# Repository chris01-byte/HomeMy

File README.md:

# HomeMy

HomeMy is a ROS 2 platform for a household robot. It is initialized as a safe, modular foundation: simulation first, explicit contracts, and controlled transfers from roboter_ws.

## Start Here

1. Read [AGENTS.md](AGENTS.md) for safety and work rules.
2. Read [CURRENT_STATE.md](CURRENT_STATE.md) for the active project state.
3. Choose one focused context area in [context/index.json](context/index.json).
4. In a local checkout, run python tools/context/brief.py --area architecture or another matching area.

## Appliance Startup

HomeMy will use one on-board Linux computer for customer operation. Developer mode retains the normal Ubuntu login and desktop. Customer mode will start the HomeMy systemd target automatically, with no customer Ubuntu login, terminal, or manual ROS command.

The customer-facing display reports boot, self-test, ready, limited-ready, or fault states with a stable error code and clear next action. The external AI server is optional for local boot: an AI outage produces limited capability, not an unsafe or blocked local startup. Power-on and ready state never authorize motion by themselves.

The current decision and contracts are [the appliance architecture decision](docs/decisions/2026-08-28-appliance-startup.md), [the system lifecycle](contracts/ros/system-lifecycle.md), [customer power-on](contracts/hardware/customer-power-on.md), and [external AI health](contracts/api/ai-server-health.md).

## Structure

| Path | Purpose |
| --- | --- |
| [src/](src/README.md) | HomeMy-owned ROS 2 packages |
| [contracts/](contracts/README.md) | Stable ROS, hardware, API, and data boundaries |
| [simulation/](simulation/README.md) | Synthetic fixtures and deterministic scenarios |
| [deployment/systemd/](deployment/systemd/README.md) | Versioned systemd target and unit templates, not yet enabled |
| [integration/roboter_ws/](integration/roboter_ws/TRANSFER_MANIFEST.md) | Controlled transfers from roboter_ws |
| [docs/](docs/README.md) | Decisions, transfers, runbooks, and archived evidence |
| [context/](context/index.json) | Token-bounded context routing for agents |
| [tools/context/](tools/context/brief.py) | Context packet generator and validator |

## Transfer Policy

HomeMy does not start as a copy of roboter_ws. Every capability transfer names an immutable source commit, target contract, dependencies, validation, risk, and rollback path before code is ported.

## Safety and Privacy

The default is simulation or motorless validation. No actor is enabled without explicit human approval. Secrets, home maps, camera data, ROS bags, and deployment-specific configuration stay outside version control.

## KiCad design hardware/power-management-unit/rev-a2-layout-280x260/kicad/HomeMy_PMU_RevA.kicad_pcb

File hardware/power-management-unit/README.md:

# HomeMy Power Management Unit (PMU)

## Verbindlicher Arbeitsstand

Die PMU ist die zentrale Energieverteilungs-, Schutz-, Mess- und Zustandssteuerung des HomeMy-Roboters.

Der nächste PCB-Arbeitsstand ist **ausschließlich 300 × 280 mm**. Frühere Verkleinerungsversuche mit 250 × 200, 275 × 210, 280 × 220 und 300 × 220 mm sind verworfen und nicht Teil dieses Arbeitsstands.

## Quellen der Wahrheit

In dieser Reihenfolge lesen:

1. `requirements.yaml` – verbindliche elektrische Werte und Statusklassen.
2. `ASTRA_PCB_HANDOFF.md` – Topologie, Schutzkonzept und Systemverhalten.
3. `interfaces-and-layout.md` – Anschlüsse, Schnittstellen und Layoutregeln.
4. `rev-a/README.md` und `rev-a/design/` – ausgearbeitete Schaltung, Bauteil- und Hochstromregeln.
5. `verification-plan.md` – Prüf- und Inbetriebnahmestrategie.
6. `ASTRA_300X280_LAYOUT.md` – begrenzter Arbeitsauftrag für das neue Layout.

## Beibehaltene Referenz

`rev-a/` ist die erfolgreiche elektrische und mechanische Referenz. Sie enthält den hierarchischen KiCad-Schaltplan, Footprints, Bauteilauswahl, Hochstromregeln, Berechnungen und überprüfbare Fertigungsgrundlagen. Ihre vorhandene Leiterplatte darf als Referenz dienen, ist aber **nicht** die Zielgeometrie des neuen Layouts.

Topologie, Netznamen, Schutzfunktionen, Bauteilwerte, Footprints, Kelvin-Verbindungen, Gate-Beschaltung, Busbar-/Press-fit-Schnittstellen und Sicherheitsregeln dürfen beim Übertragen nicht stillschweigend verändert werden.

## Aktiver Layoutauftrag

Astra erstellt einen neuen, vollständigen KiCad-PCB-Arbeitsstand in:

`hardware/power-management-unit/rev-a2-300x280/`

Die Zielkontur ist fest 300 × 280 mm. Alte kompakte Layouts dürfen weder fortgesetzt noch als CAD-Quelle kopiert werden. Der elektrische Ausgangspunkt ist der Schaltplan aus `rev-a/kicad/`.

## Freigabestatus

- Engineering-Prototyp: nach vollständiger Prüfung und menschlicher Bestellfreigabe zulässig.
- Bestromung: erst nach Schließen der in den Dokumenten genannten Energization Gates.
- Produktion/Rev B: nicht freigegeben.
- Aktorbewegung: durch diesen PCB-Auftrag nicht freigegeben.

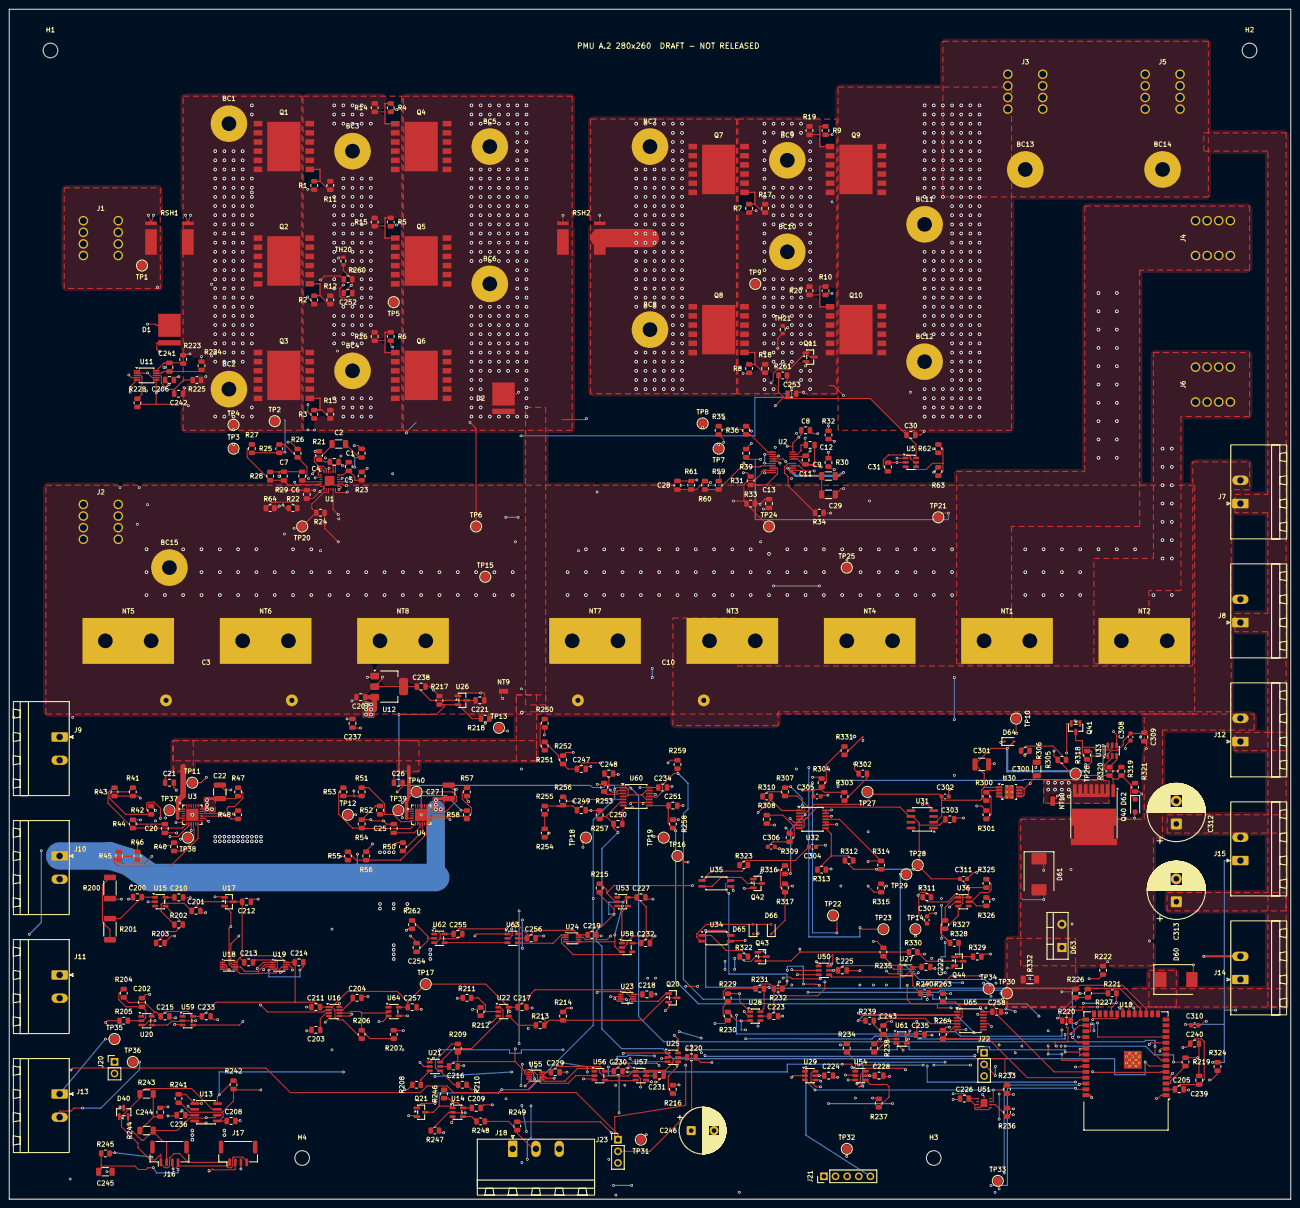
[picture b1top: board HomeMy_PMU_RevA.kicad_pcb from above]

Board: 4 copper layers, 280.0 x 260.0 mm, 425 parts (0 on the bottom side), 194 nets.

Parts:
BC1, BC2: BB1 copper clamp contact; Busbar_Contact_M3_D8
BC3, BC4: BB2 copper clamp contact; Busbar_Contact_M3_D8
BC5, BC6: BB3 copper clamp contact; Busbar_Contact_M3_D8
BC7, BC8: BB4 copper clamp contact; Busbar_Contact_M3_D8
BC9, BC10: BB5 copper clamp contact; Busbar_Contact_M3_D8
BC11, BC12, BC13, BC14: BB6 copper clamp contact; Busbar_Contact_M3_D8
BC15: BB7 copper clamp contact; Busbar_Contact_M3_D8
C1, C8, C21, C26, C30: 100nF100V X7R; C_0805_2012Metric
C2: 1uF25V X7R; C_1206_3216Metric
C3, C10: 33uF63V10% PET film; C_Rect_L31.5mm_W13mm_P27.5mm
C4, C5, C6, C7, C11, C12, C13, C31: 1nF50V5% C0G; C_0805_2012Metric
C9, C29: 4.7uF25V X7R; C_1206_3216Metric
C20, C25: 22nF50V5% C0G; C_0805_2012Metric
C22, C27: 1uF100V X7R; C_1210_3225Metric
C28: 10nF50V5% C0G; C_0805_2012Metric
C200, C205, C206, C207, C208, C209, C210, C211, C212, C213, C214, C215, C216, C217, C218, C219, C220, C221, C222, C223, C224, C225, C226, C227, C228, C229, C230, C231, C232, C233, C234, C235, C236, C240, C241, C248, C250, C251, C252, C253, C255, C256, C257, C258: 100n; C_0805_2012Metric
C201, C204, C254: 1u; C_0805_2012Metric
C202, C242, C243, C244: 10n; C_0805_2012Metric
C203: 22n; C_0805_2012Metric
C237, C238, C239: 10u; C_0805_2012Metric
C245: 1n; C_1206_3216Metric
C246: 1000u 10V; CP_Radial_D10.0mm_P5.00mm
C247, C249: 1n; C_0805_2012Metric
C300: 1uF 100V; C_1206_3216Metric
C301: 10uF 25V; C_1210_3225Metric
C302, C304, C307, C308, C310, C311: 100nF 50V; C_0603_1608Metric
C303, C309: 1uF 25V; C_0805_2012Metric
C305, C306: 100pF 50V C0G; C_0603_1608Metric
C312, C313: 470uF 100V20% high-ripple MOTION bulk; CP_Radial_D12.5mm_P5.00mm
D1, D2: 43V bidirectional low-clamp TVS; PTVS1_DFN8x6
D40: ESD2CAN24DBZRQ1; SOT-23
D60: 43V standoff TVS 1500W; D_SMC
D61: 43V drain spike clamp; D_SMC
D62: 15V gate clamp; D_SOD-123F
D63: 100V 10A resistor cable freewheel; TO-220-2_Vertical
D64: LDO reverse discharge path; D_SOD-323
D65, D66: Analog fault OR; D_SOD-323
H1, H2, H3, H4: MountingHole_3.2mm_M3
J1, J2: Battery M5 160A class; Wurth_7461103
J3: Left arm + M5 160A class; Wurth_7461103
J4: Left arm return M5 160A class; Wurth_7461103
J5: Right arm + M5 160A class; Wurth_7461103
J6: Right arm return M5 160A class; Wurth_7461103
J7: Drive 8A peak; PhoenixContact_MSTB_2,5_2-GF-5,08_1x02_P5.08mm_Horizontal_T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
J8: 24V lift-buck INPUT; PhoenixContact_MSTB_2,5_2-GF-5,08_1x02_P5.08mm_Horizontal_T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
J9: 12V PC-buck INPUT; PhoenixContact_MSTB_2,5_2-GF-5,08_1x02_P5.08mm_Horizontal_T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
J10: 5V logic-buck INPUT; PhoenixContact_MSTB_2,5_2-GF-5,08_1x02_P5.08mm_Horizontal_T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
J11: 5V converter OUTPUT return; PhoenixContact_MSTB_2,5_2-GF-5,08_1x02_P5.08mm_Horizontal_T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
J12: External resistor bank; PhoenixContact_MSTB_2,5_2-GF-5,08_1x02_P5.08mm_Horizontal_T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
J13: 24V lift clamp DNP; PhoenixContact_MSTB_2,5_2-GF-5,08_1x02_P5.08mm_Horizontal_T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
J14: Analog bank NTC; PhoenixContact_MSTB_2,5_2-GF-5,08_1x02_P5.08mm_Horizontal_T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
J15: Telemetry bank NTC; PhoenixContact_MSTB_2,5_2-GF-5,08_1x02_P5.08mm_Horizontal_T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
J16: CAN backbone IN; JST_GH_BM04B-GHS-TBT_1x04-1MP_P1.25mm_Vertical
J17: CAN backbone OUT; JST_GH_BM04B-GHS-TBT_1x04-1MP_P1.25mm_Vertical
J18: 5V LED strip 5A; PhoenixContact_MSTB_2,5_3-GF-5,08_1x03_P5.08mm_Horizontal_T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
J20: TSW-102-07-G-S; PinHeader_1x02_P2.54mm_Vertical
J21: TSW-105-07-G-S; PinHeader_1x05_P2.54mm_Vertical
J22, J23: TSW-103-07-G-S; PinHeader_1x03_P2.54mm_Vertical
NT1: ARM_L_N to BATT_N at star; NetTie_Power_2
NT2: ARM_R_N to BATT_N at star; NetTie_Power_2
NT3: DRIVE_N to BATT_N at star; NetTie_Power_2
NT4: LIFT_N to BATT_N at star; NetTie_Power_2
NT5: PC_N to BATT_N at star; NetTie_Power_2
NT6: LOGIC_BUCK_N to BATT_N at star; NetTie_Power_2
NT7: CHOPPER_N to BATT_N at star; NetTie_Power_2
NT8: LOGIC_5V_N to BATT_N at star; NetTie_Power_2
NT9: LOGIC_GND to BATT_N at star; NetTie_Logic_2
NT10: Chopper local analog reference; NetTie_Logic_2
Q1, Q2, Q3, Q4, Q5, Q6, Q7, Q8, Q9, Q10: 100V N-MOS .99mR@25C/2.3mR@175C 10V; CCPAK1212_SOT8000A
Q11: Remote temperature diode; SOT-23
Q20, Q21: BSS138BK,215; SOT-23
Q40: 100V chopper NMOS; Infineon_PG-HSOF-8-1
Q41: NTC healthy enables driver; SOT-23
Q42: Chopper gate status isolation driver; SOT-23
Q43: Qualified fault LED power; SOT-23
Q44: Qualified local enable; SOT-23
R1, R2, R3, R4, R5, R6, R7, R8, R9, R10: 10R 1%; R_0805_2012Metric
R11, R12, R13, R14, R15, R16, R17, R18, R19, R20: 10M 1%; R_0805_2012Metric
R21: 49R9 0.1% 25ppm/K; R_0805_2012Metric
R22: 18K2 0.1% 25ppm/K; R_0805_2012Metric
R23: 3K65 0.1% 25ppm/K; R_0805_2012Metric
R24, R33: 100K 0.1% 25ppm/K; R_0805_2012Metric
R25: 523K 0.1% 25ppm/K; R_0805_2012Metric
R26: 10K1 0.1% 25ppm/K; R_0805_2012Metric
R27: 732K 0.1% 25ppm/K; R_0805_2012Metric
R28, R36, R42, R44, R48, R52, R54, R58, R59, R61, R63: 10K 0.1% 25ppm/K; R_0805_2012Metric
R29, R45, R55: 1M 1%; R_0805_2012Metric
R30: 100R 0.1% 25ppm/K; R_0805_2012Metric
R31: 39K7 0.1% 25ppm/K; R_0805_2012Metric
R32: 2K74 0.1% 25ppm/K; R_0805_2012Metric
R34: 180K 1%; R_0805_2012Metric
R35, R62: 226K 0.1% 25ppm/K; R_0805_2012Metric
R39: 100K 1%; R_0805_2012Metric
R40: 6K04 0.1% 25ppm/K; R_0805_2012Metric
R41, R47, R51, R57: 191K 0.1% 25ppm/K; R_0805_2012Metric
R43, R53: 374K 0.1% 25ppm/K; R_0805_2012Metric
R46, R56: 68K 1%; R_0805_2012Metric
R50: 9K09 0.1% 25ppm/K; R_0805_2012Metric
R60: 20K 0.1% 25ppm/K; R_0805_2012Metric
R64: 200R 0.1% 25ppm/K; R_0805_2012Metric
R200, R201: 4.99k; R_2010_5025Metric
R202: 174k; R_0805_2012Metric
R203, R204, R212, R214, R219, R222, R234, R235, R236, R238, R247, R249, R250, R251, R253, R254, R255, R257, R258, R259, R263, R264: 100k; R_0805_2012Metric
R205, R218, R239, R240: 1k; R_0805_2012Metric
R206, R215: 47k; R_0805_2012Metric
R207, R209, R245: 1M; R_0805_2012Metric
R208: 120k; R_0805_2012Metric
R210: 887k; R_0805_2012Metric
R211, R213, R216, R217, R220, R221, R228, R229, R230, R231, R232, R233, R237, R241, R242, R246, R252, R256, R260, R261: 10k; R_0805_2012Metric
R223, R224, R225: 10; R_0805_2012Metric
R226, R227, R262: 4.7k; R_0805_2012Metric
R243, R244: 60.4; R_1206_3216Metric
R248: 330; R_0805_2012Metric
R300: 75.0k 0.1%; R_0805_2012Metric
R301, R304, R307, R309, R310, R311, R313, R316, R318, R324, R327: 10.0k 0.1%; R_0805_2012Metric
R302: 160k 0.1%; R_0805_2012Metric
R303: 1.40k 0.1%; R_0805_2012Metric
R305, R306: 1.00M 0.1%; R_0805_2012Metric
R308: 174k 0.1%; R_0805_2012Metric
R312: 90.9k 0.1%; R_0805_2012Metric
R314, R328: 1.00k 0.1%; R_0805_2012Metric
R315, R317, R329, R330: 100k 0.1%; R_0805_2012Metric
R319: 10.0 0.1%; R_0805_2012Metric
R320: 2.20 1%; R_0805_2012Metric
R321: 47.0k 0.1%; R_0805_2012Metric
R322, R323: 4.70k 0.1%; R_0805_2012Metric
R325: 117k 0.1%; R_0805_2012Metric
R326: 24.9k 0.1%; R_0805_2012Metric
R331: 690k 0.1%; R_0805_2012Metric
R332: 22.0k1% motion-bulk discharge; R_1206_3216Metric
RSH1, RSH2: 0.5mR 1% four-terminal10W@70C terminal; CSS4J_4026_Kelvin
TH20, TH21: 10k NTC B3380 1%; R_0603_1608Metric
TP1: BATT_FUSED_P; TestPoint_Pad_D2.0mm
TP2: BATT_SENSED_P; TestPoint_Pad_D2.0mm
TP3: MAIN_KELVIN_P; TestPoint_Pad_D2.0mm
TP4: MAIN_KELVIN_N; TestPoint_Pad_D2.0mm
TP5: MAIN_COMMON; TestPoint_Pad_D2.0mm
TP6: SYS_BUS_P; TestPoint_Pad_D2.0mm
TP7: MOTION_KELVIN_P; TestPoint_Pad_D2.0mm
TP8: MOTION_KELVIN_N; TestPoint_Pad_D2.0mm
TP9: MOTION_COMMON; TestPoint_Pad_D2.0mm
TP10: MOTION_BUS_P; TestPoint_Pad_D2.0mm
TP11: PC_BUCK_IN_P; TestPoint_Pad_D2.0mm
TP12: LOGIC_BUCK_IN_P; TestPoint_Pad_D2.0mm
TP13: V5V; TestPoint_Pad_D2.0mm
TP14: V3V3; TestPoint_Pad_D2.0mm
TP15: BATT_N; TestPoint_Pad_D2.0mm
TP16: LOGIC_GND; TestPoint_Pad_D2.0mm
TP17: AON_3V3; TestPoint_Pad_D2.0mm
TP18: AON_WAKE_EN; TestPoint_Pad_D2.0mm
TP19: MAIN_FAULT_N; TestPoint_Pad_D2.0mm
TP20: MAIN_TMR; TestPoint_Pad_D2.0mm
TP21: MOTION_GATE_EN; TestPoint_Pad_D2.0mm
TP22: MOTION_FLT_N; TestPoint_Pad_D2.0mm
TP23: MOTION_TEMP_FLT_N; TestPoint_Pad_D2.0mm
TP24: MOTION_TMR; TestPoint_Pad_D2.0mm
TP25: MOTION_IMON_INPUT; TestPoint_Pad_D2.0mm
TP26: CHOP_GATE; TestPoint_Pad_D2.0mm
TP27: CHOP_10V; TestPoint_Pad_D2.0mm
TP28: CHOP_REF2V5; TestPoint_Pad_D2.0mm
TP29: CHOP_FAULT_N; TestPoint_Pad_D2.0mm
TP30: CHOP_ACTIVE_N; TestPoint_Pad_D2.0mm
TP31: CAN_TX; TestPoint_Pad_D2.0mm
TP32: CAN_RX; TestPoint_Pad_D2.0mm
TP33: ESP_MAIN_HOLD; TestPoint_Pad_D2.0mm
TP34: ESP_MOTION_RESET; TestPoint_Pad_D2.0mm
TP35: LIFT_24V_SAMPLE; TestPoint_Pad_D2.0mm
TP36: LIFT_24V_N; TestPoint_Pad_D2.0mm
TP37: PC_EFUSE_FAULT_N; TestPoint_Pad_D2.0mm
TP38: PC_EFUSE_PGOOD; TestPoint_Pad_D2.0mm
TP39: LOGIC_EFUSE_FAULT_N; TestPoint_Pad_D2.0mm
TP40: LOGIC_EFUSE_PGOOD; TestPoint_Pad_D2.0mm
U1: LM74930-Q1; VQFN_RGE24_4x4_P0.5_EP_FLOAT
U2: TPS48110-Q1; VSSOP_DGX19_3x5.1_P0.5_Missing16
U3, U4: TPS26631 eFuse latch-off; Texas_RGE0024H_VQFN-24-1EP_4x4mm_P0.5mm_EP2.7x2.7mm
U5: Latched motion SYS undervoltage detector; SOT-23-6
U10: ESP32-S3-WROOM-1-N8; ESP32-S3-WROOM-1
U11: INA228AIDGSR; MSOP-10_3x3mm_P0.5mm
U12: TLV1117LV33DCYR; SOT-223-3_TabPin2
U13: TCAN1042HGVDRQ1; SOIC-8_3.9x4.9mm_P1.27mm
U14: SN74AHCT1G125DBVR; SOT-23-5
U15: LT3014BIS5#TRPBF; SOT-23-5
U16: LTC2954ITS8-1#TRPBF; TSOT-23-8
U17, U26: TPS3839G33DBZR; SOT-23
U18, U23, U27, U55: SN74LVC1G74DCUR; VSSOP-8_2.3x2mm_P0.5mm
U19, U24: SN74LVC2G00DCUR; VSSOP-8_2.3x2mm_P0.5mm
U20, U53, U56, U59: SN74LVC1G14DBVR; SOT-23-5
U21: LTC6993IS6-1#TRPBF; TSOT-23-6
U22, U58: SN74LVC1G32DBVR; SOT-23-5
U25, U28, U29, U50, U54, U57, U63: SN74LVC1G11DBVR; SOT-23-6
U30: 100V LDO, nominal 10V; Texas_DGN0008B_VSSOP-8-1EP_3x3mm_P0.65mm_EP2x3mm_Mask1.88x1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
U31: 2.5V high-grade reference; SOIC-8_3.9x4.9mm_P1.27mm
U32: Independent analog chopper/OV/NTC window; TSSOP-14_4.4x5mm_P0.65mm
U33: 4A source/8A sink driver; SOT-23-6
U34: Isolated analog fault; SSOP-4_4.4x2.6mm_P1.27mm
U35: Isolated chopper active; SSOP-4_4.4x2.6mm_P1.27mm
U36: Reference qualification 12..28ms; SOT-23-6
U51: TPS3431SDRBR; TI_DRB0008A_3x3mm_EP1.5x1.75
U60, U65: TMUX1511PWR; TSSOP-14_4.4x5mm_P0.65mm
U61, U62, U64: SN74LVC1G17DBVR; SOT-23-5

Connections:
AON_3V3: C201.1, C210.1, C211.1, C212.1, C213.1, C214.1, C215.1, C216.1, C217.1, C218.1, C219.1, C220.1, C227.1, C229.1, C230.1, C231.1, C232.1, C233.1, C255.1, C256.1, C257.1, R202.1, R204.1, R206.1, R209.1, R215.1, TP17.1, U15.5, U16.1, U17.3, U18.8, U19.8, U20.5, U21.5, U22.5, U23.8, U24.8, U25.5, U53.5, U55.2, U55.7, U55.8, U56.5, U57.5, U57.6, U58.5, U59.5, U62.5, U63.5, U64.5
AON_FB: R202.2, R203.1, U15.4
AON_FEED_MID: R200.2, R201.1
AON_LDO_IN: C200.1, R201.2, U15.1
AON_RESET_N: U17.2, U18.6, U19.2, U25.6, U63.6
AON_WAKE_EN: R29.1, R216.1, TP18.1, U1.6, U1.7, U25.4, U50.6, U54.6
ARM_L_N: J4.1, J4.2, J4.3, J4.4, J4.5, J4.6, J4.7, J4.8, NT1.1
ARM_R_N: J6.1, J6.2, J6.3, J6.4, J6.5, J6.6, J6.7, J6.8, NT2.1
BATT_FUSED_P: D1.1, J1.1, J1.2, J1.3, J1.4, J1.5, J1.6, J1.7, J1.8, RSH1.1, TP1.1
BATT_N: BC15.1, C1.2, C3.2, C6.2, C7.2, C8.2, C10.2, C13.2, C20.2, C21.2, C22.2, C25.2, C26.2, C27.2, C28.2, D1.2, D2.2, J2.1, J2.2, J2.3, J2.4, J2.5, J2.6, J2.7, J2.8, NT1.2, NT2.2, NT3.2, NT4.2, NT5.2, NT6.2, NT7.2, NT8.2, NT9.2, Q11.2, R24.2, R26.2, R28.2, R29.2, R31.2, R33.2, R36.2, R39.2, R40.2, R42.2, R44.2, R46.2, R48.2, R50.2, R52.2, R54.2, R56.2, R58.2, R59.2, R61.2, R64.2, TP15.1, U1.13, U1.16, U2.2, U2.6, U3.8, U3.25, U4.8, U4.25
BATT_SENSED_P: BC1.1, BC2.1, C1.1, C2.2, Q1.7, Q1.8, Q1.9, Q1.10, Q1.11, Q1.12, Q1.13, Q2.7, Q2.8, Q2.9, Q2.10, Q2.11, Q2.12, Q2.13, Q3.7, Q3.8, Q3.9, Q3.10, Q3.11, Q3.12, Q3.13, R25.1, R27.1, R200.1, R225.1, RSH1.4, TP2.1, U1.22
BUTTON_ARMED: U18.5, U19.6
BUTTON_ARM_SET_N: U18.7, U19.7
BUTTON_INT_N: R221.2, U10.23, U16.5
CAN_H: D40.1, J16.1, J17.1, R243.1, U13.7
CAN_L: D40.2, J16.2, J17.2, R244.2, U13.6
CAN_RX: TP32.1, U10.9, U13.4
CAN_STB: R242.2, U10.34, U13.8
CAN_TERM_MID: C244.1, R243.2, R244.1
CAN_TX: R241.2, TP31.1, U10.10, U13.1
CHASSIS: C245.1, J16.4, J17.4, R245.1
CHOPPER_N: C312.2, C313.2, D60.2, D61.2, NT7.1, NT10.2, Q40.2, R332.2
CHOP_10V: C301.1, C302.1, C304.1, C308.1, C309.1, D64.2, Q43.2, R300.1, R307.1, R310.1, R316.1, R318.1, R323.1, R330.1, TP27.1, U30.1, U31.2, U32.3, U33.1
CHOP_ACTIVE_LED_A: R323.2, U35.1
CHOP_ACTIVE_LED_K: Q42.3, U35.2
CHOP_ACTIVE_N: R232.2, TP30.1, U10.32, U35.4
CHOP_DISABLE: Q41.3, R318.2, U33.5
CHOP_DRAIN: D61.1, D63.2, J12.2, Q40.3
CHOP_DRIVE_H: R319.1, U33.2
CHOP_DRIVE_L: R320.1, U33.3
CHOP_FAULT_LED_A: R322.2, U34.1
CHOP_FAULT_LED_K: D65.2, D66.2, U34.2
CHOP_FAULT_N: R231.2, TP29.1, U10.31, U28.6, U34.4
CHOP_FAULT_PWR: Q43.3, R322.1
CHOP_FB: R300.2, R301.1, U30.2
CHOP_GATE: D62.1, Q40.1, Q42.1, R305.1, R319.2, R320.2, R321.1, TP26.1
CHOP_GND: C300.2, C301.2, C302.2, C303.2, C304.2, C305.2, C306.2, C307.2, C308.2, C309.2, C311.2, D62.2, J14.2, NT10.1, Q42.2, Q44.2, R301.2, R304.2, R309.2, R313.2, R315.2, R317.2, R321.2, R326.2, R329.2, U30.4, U30.9, U31.4, U32.12, U33.4, U36.2
CHOP_HYS_MID: R305.2, R306.1
CHOP_HYS_MID2: R306.2, R331.1
CHOP_NTC: C307.1, J14.1, R311.2, U32.9, U32.10
CHOP_OV_OK: D65.1, R310.2, U32.1
CHOP_OV_SENSE: C306.1, R308.2, R309.1, U32.6
CHOP_QUALIFY_BASE: Q44.1, R328.2, R329.1
CHOP_QUALIFY_N: Q41.2, Q43.1, Q44.3, R330.2
CHOP_REF2V5: C303.1, C311.1, R311.1, R312.1, R314.1, R325.1, R327.1, TP28.1, U31.6, U32.4, U32.7, U36.3, U36.6
CHOP_REF_READY: R327.2, R328.1, U36.1
CHOP_REF_SENSE: R325.2, R326.1, U36.5
CHOP_REQUEST: R307.2, U32.2, U33.6
CHOP_SENSE: C305.1, R303.2, R304.1, R331.2, U32.5
CHOP_SENSE_TOP: R302.2, R303.1
CHOP_TEMP_ADC: C310.1, J15.1, R324.2, U10.4
CHOP_TEMP_HIGH: R314.2, R315.1, U32.11
CHOP_TEMP_LOW: R312.2, R313.1, U32.8
CHOP_THERMAL_OK: D66.1, Q41.1, R316.2, R317.1, U32.13, U32.14
DRIVE_N: J7.2, NT3.1
ESP_BOOT_N: J21.4, R220.2, U10.27
ESP_CHIP_EN: J21.5, R218.2, R219.1, U10.3, U29.1
ESP_MAIN_HOLD: R211.1, R222.1, TP33.1, U10.22
ESP_MAIN_HOLD_AON: R211.2, R212.1, U22.2
ESP_MOTION_REQUEST: R234.1, U10.19, U54.1
ESP_MOTION_RESET: R235.1, TP34.1, U10.20, U27.1
ESP_UART_RX: R263.1, U10.36, U65.3
ESP_UART_TX: R264.1, U10.37, U65.6
ESP_WDI: R236.1, U10.21, U51.6
ESP_WDO_N: R233.2, U29.3, U51.7
I2C_SCL: J23.2, R227.2, U10.18, U11.5
I2C_SDA: J23.1, R226.2, U10.17, U11.4
INA_ALERT_N: R228.2, U10.33, U11.3
INA_IN_N: C241.2, R224.2, U11.9
INA_IN_P: C241.1, R223.2, U11.10
INA_VBUS: C242.1, R225.2, U11.8
KILL_HOLD_OR: R213.1, U22.4
LED_BUFFER_OUT: R248.1, U14.4
LED_DATA_3V3: R247.1, U10.11, U14.2
LED_DATA_OUT: J18.2, R248.2, R249.1
LED_OE_N: Q21.3, R246.2, U14.1
LIFT_24V_N: J13.2, TP36.1
LIFT_24V_SAMPLE: J13.1, TP35.1
LIFT_N: J8.2, NT4.1
LOGIC_5V_N: C246.2, J11.2, J18.3, NT8.1
LOGIC_BUCK_IN_P: C27.1, J10.1, R57.1, TP12.1, U4.17, U4.18
LOGIC_BUCK_N: J10.2, NT6.1
LOGIC_DVDT: C25.1, U4.9
LOGIC_EFUSE_FAULT_N: TP39.1, U4.14
LOGIC_EFUSE_PGOOD: TP40.1, U4.16
LOGIC_GND: C30.2, C31.2, C200.2, C201.2, C202.2, C203.2, C204.2, C205.2, C206.2, C207.2, C208.2, C209.2, C210.2, C211.2, C212.2, C213.2, C214.2, C215.2, C216.2, C217.2, C218.2, C219.2, C220.2, C221.2, C222.2, C223.2, C224.2, C225.2, C226.2, C227.2, C228.2, C229.2, C230.2, C231.2, C232.2, C233.2, C234.2, C235.2, C236.2, C237.2, C238.2, C239.2, C240.2, C242.2, C243.2, C244.2, C245.2, C247.2, C248.2, C249.2, C250.2, C251.2, C252.2, C253.2, C254.2, C255.2, C256.2, C257.2, C258.2, C310.2, D40.3, J15.2, J16.3, J17.3, J20.2, J21.1, J22.3, J23.3, NT9.1, Q20.2, Q21.2, R63.2, R203.2, R207.2, R208.2, R210.2, R212.2, R214.2, R216.2, R217.2, R219.2, R222.2, R234.2, R235.2, R236.2, R237.2, R238.2, R245.2, R247.2, R249.2, R252.2, R253.2, R256.2, R257.2, R258.2, R259.2, R263.2, R264.2, TH20.2, TH21.2, TP16.1, U5.2, U10.1, U10.40, U10.41, U11.1, U11.2, U11.7, U12.1, U13.2, U14.3, U15.2, U16.4, U17.1, U18.1, U18.2, U18.4, U19.4, U20.3, U21.2, U22.3, U23.1, U23.2, U23.4, U24.4, U24.5, U24.6, U25.2, U26.1, U27.4, U28.2, U29.2, U34.3, U35.3, U50.2, U51.4, U51.9, U53.3, U54.2, U55.4, U56.3, U57.2, U58.3, U59.3, U60.7, U61.3, U62.3, U63.2, U64.3, U65.7, U65.10, U65.13
LOGIC_ILIM: R50.1, U4.10
LOGIC_OVP: R53.2, R54.1, U4.7
LOGIC_PGTH: R57.2, R58.1, U4.15
LOGIC_SHDN: R55.2, R56.1, U4.12
LOGIC_UVLO: R51.2, R52.1, U4.6
MAIN_CAP: C2.1, U1.23
MAIN_CAPTURE_DELAYED: U62.4, U63.3
MAIN_CAPTURE_EN: U24.1, U63.4
MAIN_CAPTURE_RC: C254.1, R262.2, U62.2
MAIN_COMMON: BC3.1, BC4.1, Q1.2, Q1.3, Q1.4, Q1.5, Q1.6, Q2.2, Q2.3, Q2.4, Q2.5, Q2.6, Q3.2, Q3.3, Q3.4, Q3.5, Q3.6, Q4.2, Q4.3, Q4.4, Q4.5, Q4.6, Q5.2, Q5.3, Q5.4, Q5.5, Q5.6, Q6.2, Q6.3, Q6.4, Q6.5, Q6.6, R11.2, R12.2, R13.2, R14.2, R15.2, R16.2, TP5.1, U1.2, U1.15
MAIN_CS_P: C4.1, R21.2, U1.20
MAIN_DGATE: R4.1, R5.1, R6.1, U1.1
MAIN_FAULT_ANY: U24.2, U58.4
MAIN_FAULT_ASSERTED: U53.4, U58.1
MAIN_FAULT_GPIO_N: R259.1, U10.28, U60.11
MAIN_FAULT_LATCHED: Q20.1, U23.5
MAIN_FAULT_N: R215.2, TP19.1, U1.12, U53.2, U60.12
MAIN_FAULT_SET_N: U23.7, U24.7
MAIN_HGATE: R1.1, R2.1, R3.1, U1.14
MAIN_ILIM: R22.1, U1.11
MAIN_ILIM_TAIL: R22.2, R64.1
MAIN_ISCP: C5.1, R23.2, U1.18
MAIN_KELVIN_N: C4.2, C5.2, R224.1, RSH1.3, TP4.1, U1.19
MAIN_KELVIN_P: R21.1, R23.1, R223.1, RSH1.2, TP3.1
MAIN_LATCH_OK: U23.3, U25.3
MAIN_OV: C7.1, R27.2, R28.1, U1.5
MAIN_TMR: C3.1, R24.1, TP20.1, U1.9
MAIN_UVLO: C6.1, R25.2, R26.1, U1.4
MOTION_ARMED: R240.1, U27.5, U54.3
MOTION_ARMED_SENSE: R240.2, U10.35
MOTION_BST: C9.1, C29.1, U2.12
MOTION_BUS_ADC: C250.1, R257.1, U10.6, U60.6
MOTION_BUS_DIV: C249.1, R255.2, R256.1, U60.5
MOTION_BUS_P: BC11.1, BC12.1, BC13.1, BC14.1, C300.1, C312.1, C313.1, D60.1, D63.1, D64.1, J3.1, J3.2, J3.3, J3.4, J3.5, J3.6, J3.7, J3.8, J5.1, J5.2, J5.3, J5.4, J5.5, J5.6, J5.7, J5.8, J7.1, J8.1, J12.1, Q9.7, Q9.8, Q9.9, Q9.10, Q9.11, Q9.12, Q9.13, Q10.7, Q10.8, Q10.9, Q10.10, Q10.11, Q10.12, Q10.13, R254.1, R302.1, R308.1, R332.1, TP10.1, U30.5, U30.8
MOTION_CLEAR_N: U27.6, U50.4
MOTION_COMMON: BC9.1, BC10.1, C9.2, C29.2, Q7.2, Q7.3, Q7.4, Q7.5, Q7.6, Q8.2, Q8.3, Q8.4, Q8.5, Q8.6, Q9.2, Q9.3, Q9.4, Q9.5, Q9.6, Q10.2, Q10.3, Q10.4, Q10.5, Q10.6, R17.2, R18.2, R19.2, R20.2, TP9.1, U2.13
MOTION_CS_P: C11.1, R30.2, U2.18
MOTION_FAULTS_OK: U28.4, U50.3
MOTION_FLT_N: R229.2, TP22.1, U2.5, U5.1, U10.29, U28.1
MOTION_GATE_DRIVE: R7.1, R8.1, R9.1, R10.1, R34.2, U2.14
MOTION_GATE_EN: R39.1, R237.1, TP21.1, U2.3, U54.4
MOTION_IMON_ADC: C251.1, R258.1, U10.5, U60.8
MOTION_IMON_INPUT: C28.1, R60.2, R61.1, TP25.1, U60.9
MOTION_IMON_RAW: R59.1, R60.1, U2.7
MOTION_ISCP: C12.1, R32.2, U2.19
MOTION_IWRN: R31.1, U2.8
MOTION_KELVIN_N: C11.2, C12.2, RSH2.3, TP8.1, U2.17
MOTION_KELVIN_P: R30.1, R32.1, RSH2.2, TP7.1
MOTION_LATCH_UV_SENSE: R62.2, R63.1, U5.3
MOTION_LOCAL_OK: U29.4, U50.1
MOTION_PERMIT: U29.6, U61.4
MOTION_PERMIT_CONNECTOR: J22.2, R239.1
MOTION_PERMIT_RAW: C243.1, R238.1, R239.2, U61.2
MOTION_PU: R34.1, U2.15
MOTION_SENSED_P: BC7.1, BC8.1, Q7.7, Q7.8, Q7.9, Q7.10, Q7.11, Q7.12, Q7.13, Q8.7, Q8.8, Q8.9, Q8.10, Q8.11, Q8.12, Q8.13, RSH2.4
MOTION_TEMP_DIODE: C13.1, Q11.1, Q11.3, U2.10
MOTION_TEMP_FLT_N: R230.2, TP23.1, U2.4, U10.30, U28.3
MOTION_TMR: C10.1, R33.1, TP24.1, U2.9
MOTION_UVLO: R35.2, R36.1, U2.1
MOTION_UV_REF: C31.1, U5.4, U5.5
MOT_DIV_MID: R254.2, R255.1
PB_CONNECTOR: J20.1, R205.1
PB_LTC_N: U16.2, U19.3
PB_PRESSED: U19.5, U20.4, U59.2
PB_RAW_N: C202.1, R204.2, R205.2, U20.2
PB_RELEASED: U19.1, U59.4
PC_BUCK_IN_P: C22.1, J9.1, R47.1, TP11.1, U3.17, U3.18
PC_DVDT: C20.1, U3.9
PC_EFUSE_FAULT_N: TP37.1, U3.14
PC_EFUSE_PGOOD: TP38.1, U3.16
PC_ILIM: R40.1, U3.10
PC_N: J9.2, NT5.1
PC_OVP: R43.2, R44.1, U3.7
PC_PGTH: R47.2, R48.1, U3.15
PC_SHDN: R45.2, R46.1, U3.12
PC_UVLO: R41.2, R42.1, U3.6
Q1_G: Q1.1, R1.2, R11.1
Q2_G: Q2.1, R2.2, R12.1
Q3_G: Q3.1, R3.2, R13.1
Q4_G: Q4.1, R4.2, R14.1
Q5_G: Q5.1, R5.2, R15.1
Q6_G: Q6.1, R6.2, R16.1
Q7_G: Q7.1, R7.2, R17.1
Q8_G: Q8.1, R8.2, R18.1
Q9_G: Q9.1, R9.2, R19.1
Q10_G: Q10.1, R10.2, R20.1
STARTUP_DIV: R209.2, R210.1, U21.4
STARTUP_GRANT: U21.6, U22.1
STARTUP_RSET: R208.1, U21.3
SW_BROWNOUT: U57.4, U58.2
SW_POWER_SEEN: U55.5, U57.1
SW_RESET_ASSERTED: U56.4, U57.3
SW_RESET_N: Q21.1, R217.1, R218.1, U26.2, U55.1, U56.2, U60.1, U60.4, U60.10, U60.13, U65.1, U65.4
SYS_BUS_ADC: C248.1, R253.1, U10.7, U60.3
SYS_BUS_DIV: C247.1, R251.2, R252.1, U60.2
SYS_BUS_P: BC5.1, BC6.1, C8.1, C21.1, C26.1, D2.1, Q4.7, Q4.8, Q4.9, Q4.10, Q4.11, Q4.12, Q4.13, Q5.7, Q5.8, Q5.9, Q5.10, Q5.11, Q5.12, Q5.13, Q6.7, Q6.8, Q6.9, Q6.10, Q6.11, Q6.12, Q6.13, R35.1, R41.1, R43.1, R45.1, R51.1, R53.1, R55.1, R62.1, R250.1, RSH2.1, TP6.1, U1.24, U2.20, U3.1, U3.2, U3.5, U4.1, U4.2, U4.5
SYS_DIV_MID: R250.2, R251.1
TEMP_MAIN_ADC: C252.1, R260.2, TH20.1, U10.39
TEMP_MOTION_ADC: C253.1, R261.2, TH21.1, U10.38
UART_RX_CONNECTOR: J21.2, U65.2
UART_TX_CONNECTOR: J21.3, U65.5
V3V3: C30.1, C205.1, C206.1, C208.1, C221.1, C222.1, C223.1, C224.1, C225.1, C226.1, C228.1, C234.1, C235.1, C238.1, C239.1, C240.1, C258.1, J22.1, R220.1, R221.1, R226.1, R227.1, R228.1, R229.1, R230.1, R231.1, R232.1, R233.1, R241.1, R242.1, R260.1, R261.1, R324.1, TP14.1, U5.6, U10.2, U11.6, U12.2, U13.5, U26.3, U27.2, U27.7, U27.8, U28.5, U29.5, U50.5, U51.1, U51.3, U51.5, U54.5, U60.14, U61.5, U65.14
V5V: C207.1, C209.1, C236.1, C237.1, C246.1, J11.1, J18.1, R246.1, TP13.1, U12.3, U13.3, U14.5
WAKE_EN_OD: R206.2, R207.1, U16.6, U64.2
WAKE_KILL: Q20.3, R213.2, R214.1, U16.8
WAKE_ONT: C203.1, U16.3
WAKE_PDT: C204.1, U16.7
WAKE_RAW_EN: R262.1, U21.1, U23.6, U25.1, U55.6, U63.1, U64.4

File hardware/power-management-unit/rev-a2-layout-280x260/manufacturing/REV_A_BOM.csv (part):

references,quantity_positions,quantity_required,unit,mpn,manufacturer,footprint,descriptions,ratings,dnp,population,lifecycle,source_urls,evidence_documents,alternatives,order_code_review,supplier_stock_verified,stock_status,notes,sheets,state
J7; J8; J9; J10; J11; J12; J14; J15,8,8,each,1776508,Phoenix Contact,"Connector_Phoenix_MSTB:PhoenixContact_MSTB_2,5_2-GF-5,08_1x02_P5.08mm_Horizontal_ThreadedFlange",5V converter OUTPUT return; 5V logic-buck INPUT; 12V PC-buck INPUT; 24V lift-buck INPUT; Analog bank NTC; Drive 8A peak; External resistor bank; Telemetry bank NTC,2position5.08mm threaded-flange header;12A component rating; mate1777989,false,POPULATE,Manufacturer catalog/family evidence; exact lifecycle flag not independently established,https://www.phoenixcontact.com/en-us/products/pcb-header-mst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,design/CHOPPER_PROCUREMENT.md,,Preserved exact source-record MPN; manufacturer evidence linked; supplier stock unverified,false,unverified_at_build,"12A header; mating screw-flanged plug1777989. 0.75mm2;3A input.; 12A header; mating screw-flanged plug1777989. 1.0mm2;2A provisional input.; 12A header; mating screw-flanged plug1777989. 1.0mm2;5A input to board; key separately fromJ10.; 12A header; mating screw-flanged plug1777989. 1.0mm2;5A provisional input.; 12A header; mating screw-flanged plug1777989. 1.5mm2 high-temp twisted pair; neither pin is ground.; 12A header; mating screw-flanged plug1777989. 1.5mm2 trunk.; 12A header; mating screw-flanged plug1777989. NTCLE100E3103GB0,10k2%; electrically insulated to hotter resistor chassis.; 12A header; mating screw-flanged plug1777989. Second NTCLE100E3103GB0; no shared sensor or local wiring withJ14. Grounds ultimately join at the systemstar.",09_connectors_testpoints,DRAFT_NOT_RELEASED_A2_280x260
J13,1,0,each,1776508,Phoenix Contact,"Connector_Phoenix_MSTB:PhoenixContact_MSTB_2,5_2-GF-5,08_1x02_P5.08mm_Horizontal_ThreadedFlange",24V lift clamp DNP,2position5.08mm threaded-flange header;12A component rating; mate1777989,true,DNP,Manufacturer catalog/family evidence; exact lifecycle flag not independently established,https://www.phoenixcontact.com/en-us/products/pcb-header-mst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,design/CHOPPER_PROCUREMENT.md,,Preserved exact source-record MPN; manufacturer evidence linked; supplier stock unverified,false,unverified_at_build,12A header; mating screw-flanged plug1777989. Sample external converter OUTPUT only; separately keyed.,09_connectors_testpoints,DRAFT_NOT_RELEASED_A2_280x260
J18,1,1,each,1776511,Phoenix Contact,"Connector_Phoenix_MSTB:PhoenixContact_MSTB_2,5_3-GF-5,08_1x03_P5.08mm_Horizontal_ThreadedFlange",5V LED strip 5A,3position5.08mm threaded-flange header;12A component rating; mate1777992,false,POPULATE,Manufacturer catalog/family evidence; exact lifecycle flag not independently established,https://www.phoenixcontact.com/en-au/products/pcb-header-mst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,design/CHOPPER_PROCUREMENT.md,,Preserved exact source-record MPN; manufacturer evidence linked; supplier stock unverified,false,unverified_at_build,"12A rated; mating1777992 screw-flanged plug. 1mm2 power/return;0.25mm2 data. LED return is LOGIC_5V_N direct broad copper toJ11.2/NT8; data reference meetsLOGIC_GND atsystemstar, never viaNT9 smallsignalneck.",09_connectors_testpoints,DRAFT_NOT_RELEASED_A2_280x260
D64; D65; D66,3,3,each,1N4148WS-E3-08,Vishay,Diode_SMD:D_SOD-323,Analog fault OR; LDO reverse discharge path,Analog fault OR; LDO reverse discharge path,false,POPULATE,Manufacturer catalog/family evidence; exact lifecycle flag not independently established,https://www.vishay.com/docs/85751/1n4148ws.pdf,design/CHOPPER_PROCUREMENT.md,,Preserved exact source-record MPN; manufacturer evidence linked; supplier stock unverified,false,unverified_at_build,"Cathode1,anode2.",04_brake_chopper_p1,DRAFT_NOT_RELEASED_A2_280x260
Q41; Q42,2,2,each,"2N7002,215",Nexperia,Package_TO_SOT_SMD:SOT-23,Chopper gate status isolation driver; NTC healthy enables driver,Chopper gate status isolation driver; NTC healthy enables driver,false,POPULATE,Manufacturer catalog/family evidence; exact lifecycle flag not independently established,https://assets.nexperia.com/documents/data-sheet/2N7002.pdf,design/CHOPPER_PROCUREMENT.md,,Preserved exact source-record MPN; manufacturer evidence linked; supplier stock unverified,false,unverified_at_build,,04_brake_chopper_p1,DRAFT_NOT_RELEASED_A2_280x260
J1; J2; J3; J4; J5; J6,6,6,each,7461103,Wurth Elektronik,PMU:Wurth_7461103,Battery M5 160A class; Left arm + M5 160A class; Left arm return M5 160A class; Right arm + M5 160A class; Right arm return M5 160A class,M5 press-fit160A component class;2.2Nm maximum; no soldering; qualified finished holes and insertion,false,POPULATE,Manufacturer catalog/family evidence; exact lifecycle flag not independently established,https://www.we-online.com/components/products/datasheet/7461103.pdf,design/CHOPPER_PROCUREMENT.md,,Preserved exact source-record MPN; manufacturer evidence linked; supplier stock unverified,false,unverified_at_build,"All8 pins same potential; exact qualified press-fit drill; lug6mm2; insulated cover;2.2Nm maximum torque.; Same qualified M5 press-fit terminal as battery.4mm2 cable with M5 ring lug;25A prototype envelope,temperature validation. KDSP4/1 1714029 is an alternate requiring another footprint.",09_connectors_testpoints,DRAFT_NOT_RELEASED_A2_280x260
J16; J17,2,2,each,BM04B-GHS-TBT(LF)(SN),JST,Connector_JST:JST_GH_BM04B-GHS-TBT_1x04-1MP_P1.25mm_Vertical,CAN backbone IN; CAN backbone OUT,CAN backbone IN; CAN backbone OUT,false,POPULATE,Manufacturer catalog/family evidence; exact lifecycle flag not independently established,https://www.jst-mfg.com/product/pdf/eng/eGH.pdf,design/CHOPPER_PROCUREMENT.md,,Preserved exact source-record MPN; manufacturer evidence linked; supplier stock unverified,false,unverified_at_build,Mating GHR-04V-S housing and SSHL-002T-P0.2 contacts. Linear CAN backbone; short parallel link across board; shield to CHASSIS strategy in CAN sheet.,09_connectors_testpoints,DRAFT_NOT_RELEASED_A2_280x260
Q20; Q21,2,2,each,"BSS138BK,215",Nexperia,Package_TO_SOT_SMD:SOT-23,"BSS138BK,215","BSS138BK,215",false,POPULATE,Manufacturer active/production; verify before order [source-record observation],https://assets.nexperia.com/documents/data-sheet/BSS138BK.pdf,design/WAKE_IO.md,,Preserved exact source-record MPN; manufacturer evidence linked; supplier stock unverified,false,unverified_at_build,Main fault directly sinks KILL. Final main AND also disables LM before KILL blanking expires. Logic-level2.5V RDS(on)rating6.5ohmmax; below0.01V atsub-mAloads.; Only turns LED buffer on after valid switched3V3. Logic-level2.5V RDS(on)rating6.5ohmmax; below0.01V atsub-mAloads.,06a_aon_wake_p1; 08_can_led_io,DRAFT_NOT_RELEASED_A2_280x260
Q43,1,1,each,"BSS84,215",Nexperia,Package_TO_SOT_SMD:SOT-23,Qualified fault LED power,Qualified fault LED power,false,POPULATE,Manufacturer catalog/family evidence; exact lifecycle flag not independently established,https://assets.nexperia.com/documents/data-sheet/BSS84.pdf,design/CHOPPER_PROCUREMENT.md,,Preserved exact source-record MPN; manufacturer evidence linked; supplier stock unverified,false,unverified_at_build,"PMOS gate1,source2,drain3. Body diode points from qualified rail to10V.",04_brake_chopper_p1,DRAFT_NOT_RELEASED_A2_280x260
D62,1,1,each,"BZT52H-C15,115",Nexperia,Diode_SMD:D_SOD-123F,15V gate clamp,15V gate clamp,false,POPULATE,Manufacturer catalog/family evidence; exact lifecycle flag not independently established,https://assets.nexperia.com/documents/data-sheet/BZT52H_SER.pdf,design/CHOPPER_PROCUREMENT.md,,Preserved exact source-record MPN; manufacturer evidence linked; supplier stock unverified,false,unverified_at_build,Pin1 cathode.,04_brake_chopper_p1,DRAFT_NOT_RELEASED_A2_280x260
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
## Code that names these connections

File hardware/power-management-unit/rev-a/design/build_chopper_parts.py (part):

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    {1:'MOTION_BUS_P',2:'CHOPPER_N'},'https://www.littelfuse.com/~/media/electronics/datasheets/tvs_diodes/littelfuse_tvs_diode_smcj_datasheet.pdf.pdf',
    'Pin1 cathode. Clamp69.4V at21.7A per10/1000us rating; not a braking resistor; local motion bus only.')
add('D61','SMCJ43A','43V drain spike clamp','Diode_SMD:D_SMC',
    {1:'CHOP_DRAIN',2:'CHOPPER_N'},'https://www.littelfuse.com/~/media/electronics/datasheets/tvs_diodes/littelfuse_tvs_diode_smcj_datasheet.pdf.pdf','Pin1 cathode.')
add('D62','BZT52H-C15,115','15V gate clamp','Diode_SMD:D_SOD-123F',
    {1:'CHOP_GATE',2:G},'https://assets.nexperia.com/documents/data-sheet/BZT52H_SER.pdf','Pin1 cathode.')
add('D63','MBR10100-M3/4W','100V 10A resistor cable freewheel','Package_TO_SOT_THT:TO-220-2_Vertical',
    {1:'MOTION_BUS_P',2:'CHOP_DRAIN'},'https://www.vishay.com/docs/89193/mbr10100.pdf',
    'Manufacturer pin1 and metal tab CATHODE, pin2 ANODE: verified visual page1. Keep exposed live tab isolated.')
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    add(ref,'7461103','Battery M5 160A class','PMU:Wurth_7461103',
        {i:net for i in range(1,9)},'https://www.we-online.com/components/products/datasheet/7461103.pdf',
        'All8 pins same potential; exact qualified press-fit drill; lug6mm2; insulated cover;2.2Nm maximum torque.')
for ref,net,label in [('J3','MOTION_BUS_P','Left arm +'),('J4','ARM_L_N','Left arm return'),('J5','MOTION_BUS_P','Right arm +'),('J6','ARM_R_N','Right arm return')]:
    add(ref,'7461103',label+' M5 160A class','PMU:Wurth_7461103',
        {i:net for i in range(1,9)},'https://www.we-online.com/components/products/datasheet/7461103.pdf',
        'Same qualified M5 press-fit terminal as battery.4mm2 cable with M5 ring lug;25A prototype envelope,temperature validation. KDSP4/1 1714029 is an alternate requiring another footprint.')
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plug('J9','12V PC-buck INPUT',{1:'PC_BUCK_IN_P',2:'PC_N'},'0.75mm2;3A input.')
plug('J10','5V logic-buck INPUT',{1:'LOGIC_BUCK_IN_P',2:'LOGIC_BUCK_N'},'1.0mm2;2A provisional input.')
plug('J11','5V converter OUTPUT return',{1:'+5V',2:'LOGIC_5V_N'},'1.0mm2;5A input to board; key separately fromJ10.')
plug('J12','External resistor bank',{1:'MOTION_BUS_P',2:'CHOP_DRAIN'},'1.5mm2 high-temp twisted pair; neither pin is ground.')
plug('J13','24V lift clamp DNP',{1:'LIFT_24V_SAMPLE',2:'LIFT_24V_N'},'Sample external converter OUTPUT only; separately keyed.',dnp=True)
plug('J14','Analog bank NTC',{1:'CHOP_NTC',2:G},'NTCLE100E3103GB0,10k2%; electrically insulated to hotter resistor chassis.')
plug('J15','Telemetry bank NTC',{1:'CHOP_TEMP_ADC',2:'LOGIC_GND'},'Second NTCLE100E3103GB0; no shared sensor or local wiring withJ14. Grounds ultimately join at the systemstar.')
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
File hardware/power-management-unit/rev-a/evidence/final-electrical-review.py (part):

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   c['value']='10k';c['mpn']='RC0805FR-0710KL'
   if 'Final review:10k' not in c['notes']:c['notes']+=' Final review:10k default-low for aggregate powered-off leakage; replaces100k.'
  if c['ref']=='C246':
   c['pins']['2']='LOGIC_5V_N'
   c['notes']='AtLEDconnector; height20mm maximum assumed. ReturndirectlytoLOGIC_5V_N withJ18, bypassinglogicstarNT9.'
 p.write_text(json.dumps(d,indent=2,ensure_ascii=False)+'\n')
spec=importlib.util.spec_from_file_location('schematic_review',ROOT/'scripts/build_schematic.py')
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 checks.append({'check':name,'pass':bool(passed),'detail':detail})
check('unique_references',len(parts)==len(by),len(parts))
check('explicit_DNP_selection',{c['ref'] for c in parts if c.get('dnp')}=={'R243','R244','C244','J13'},[c['ref'] for c in parts if c.get('dnp')])
check('aliases_normalized',not any(n in ('+3V3','+5V') for c in parts for n in c['pins'].values()),'V3V3/V5V only')
check('no_connect_not_real_net',not any(n and str(n).startswith('NC_') for c in parts for n in c['pins'].values()),'No-connect source placeholders converted to null')
ground_pairs=[('ARM_L_N','BATT_N'),('ARM_R_N','BATT_N'),('DRIVE_N','BATT_N'),('LIFT_N','BATT_N'),('PC_N','BATT_N'),('LOGIC_BUCK_N','BATT_N'),('CHOPPER_N','BATT_N'),('LOGIC_5V_N','BATT_N'),('LOGIC_GND','BATT_N'),('CHOP_GND','CHOPPER_N')]
for i,(a,b) in enumerate(ground_pairs,1):
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 check('critical_pin_nets_'+ref,not diff,diff or 'Matched explicit reviewed net map')
for ref in ('U3','U4'):
 check(ref+'_latch_mode',by[ref]['pins']['11'] is None and by[ref]['pins']['12'].endswith('_SHDN'),'MODE floating; SHDN passive SYS divider')
check('chopper_reference_testpoint',any(c['ref'].startswith('TP') and c['pins'].get('1')=='CHOP_REF2V5' for c in parts),'Source net CHOP_REF2V5, not CHOP_REF_2V5')
check('LED_bulk_return',by['C246']['pins']['2']=='LOGIC_5V_N',by['C246']['pins'])
check('external_optos_meaningful_ERC',all(by[r]['pin_types']['4']=='open_collector' for r in ('U34','U35')),{r:by[r]['pin_types']['4'] for r in ('U34','U35')})
# Exhaustive stable-state Boolean motion permission, independently expressed.
cases=0;fail=0
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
